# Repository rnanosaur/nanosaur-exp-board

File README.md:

# :sauropod: nanosaur expansion board - [![CC BY-NC-SA 4.0][cc-by-nc-sa-image]][cc-by-nc-sa]

NanoSaur is a little tracked robot ROS2 enabled, made for an NVIDIA Jetson Nano

* Website: [nanosaur.ai](https://nanosaur.ai)
* Do you need an help? [Discord](https://discord.gg/NSrC52P5mw)
* For technical details follow [wiki](https://github.com/rnanosaur/nanosaur/wiki)
* Something wrong? Open an [issue](https://github.com/rnanosaur/nanosaur/issues)

# How make Nanosaur PCBs on PCBWay

- Register to PCBWay using [my refferer link](https://www.pcbway.com/setinvite.aspx?inviteid=472567)
- Upon you registered, go to the <a href="https://www.pcbway.com/project/shareproject/Nanosaur___The_smallest_NVIDIA_Jetson_dinosaur_robot.html">nanosaur </a>
- Click on **"Add to Cart"** button on the right
- A pop-up will show up: all default settings are good. You must only select how many PCBs you want: the minimum quantity, by default, is 5. The first order of 5 PCBs is free on PCBWay: you must pay only the shipping costs

# Board design

This board is a simple adapter to connect the motor controller and the LCDs to the NVIDIA Jetson on your NanoSaur, this board connect:

* I2C bus 0 (Pin 27, 28)
  * oled right
* I2C bus 1 (Pin 3, 5)
  * oled left
  * adafruit motor control
* 2 custom buttons
  * GPIO Pin 31
  * GPIO Pin 33

## NVIDIA Jetson Reference

* Jetsonhacks [Jetson Nano pinout](https://www.jetsonhacks.com/nvidia-jetson-nano-j41-header-pinout/)

## Expansion board reference

Watch the documentation on [nanosaur expansion board](https://nanosaur.ai/expansion-board/)

### PCB

Layout PCB

# Develop

The documentation is made using [Kicad](https://www.kicad.org/) 5

The CI is made using
* [Kibot](https://github.com/INTI-CMNB/KiBot)
* [kicad-exports](https://github.com/nerdyscout/kicad-exports)

# License

This project is under license [Creative Commons Attribution-NonCommercial-ShareAlike 4.0 International License][cc-by-nc-sa].

[cc-by-nc-sa]: http://creativecommons.org/licenses/by-nc-sa/4.0/
[cc-by-nc-sa-image]: https://licensebuttons.net/l/by-nc-sa/4.0/88x31.png
[cc-by-nc-sa-shield]: https://img.shields.io/badge/License-CC%20BY--NC--SA%204.0-lightgrey.svg

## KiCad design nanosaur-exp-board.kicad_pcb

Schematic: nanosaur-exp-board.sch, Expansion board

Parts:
J1: jetson_nano; PinSocket_2x20_P2.54mm_Vertical
J2: Screw_Terminal_01x02; TerminalBlock_Phoenix_MPT-0,5-2-2.54_1x02_P2.54mm_Horizontal
J3, J4: Conn_i2c_oled; PinHeader_1x04_P2.54mm_Vertical
J5: Conn_motors; PinHeader_1x06_P2.54mm_Vertical
J6: Conn_buttons; PinHeader_1x03_P2.54mm_Vertical
J7: Conn_01x04; PinHeader_1x04_P2.54mm_Vertical
R1, R2: 1k; R_Axial_DIN0207_L6.3mm_D2.5mm_P10.16mm_Horizontal
SW1: SW_SPDT; slide_switch_4.7mm

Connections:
+3V3: J1.1 (3V3), J1.17 (3V3), J3.3, J4.3, J5.5, J7.3, R1.1, R2.1
GND: J1.6 (GND), J1.9 (GND), J1.14 (GND), J1.20 (GND), J1.25 (GND), J1.30 (GND), J1.34 (GND), J1.39 (GND), J2.1, J3.4, J4.4, J5.2, J5.6, J6.3, J7.4
unnamed: J1.3 (I2C_BUS1-SDA2), J4.1, J5.3, J7.1
unnamed: J1.5 (I2C_BUS1-SCL2), J4.2, J5.4, J7.2
unnamed: J1.27 (I2C_BUS0-SDA1), J3.1
unnamed: J1.28 (I2C_BUS0-SCL1), J3.2
unnamed: J1.31 (GPIO_PZ0), J6.1, R2.2
unnamed: J1.33 (GPIO_PE6), J6.2, R1.2
unnamed: J2.2, SW1.2 (B)
VCC: J1.2 (5V), J1.4 (5V), J5.1, SW1.1 (A)

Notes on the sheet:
Motors
Buttons
Display left
Display right
Optional I2C

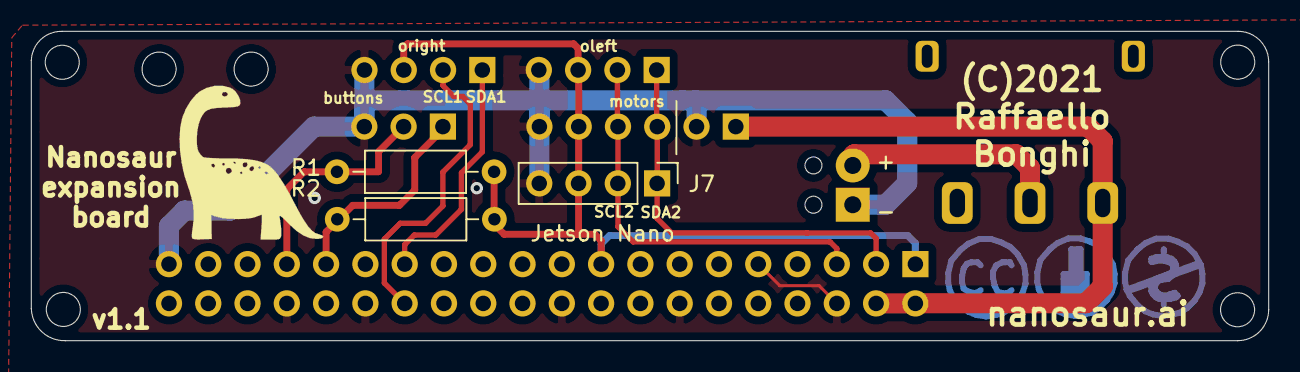
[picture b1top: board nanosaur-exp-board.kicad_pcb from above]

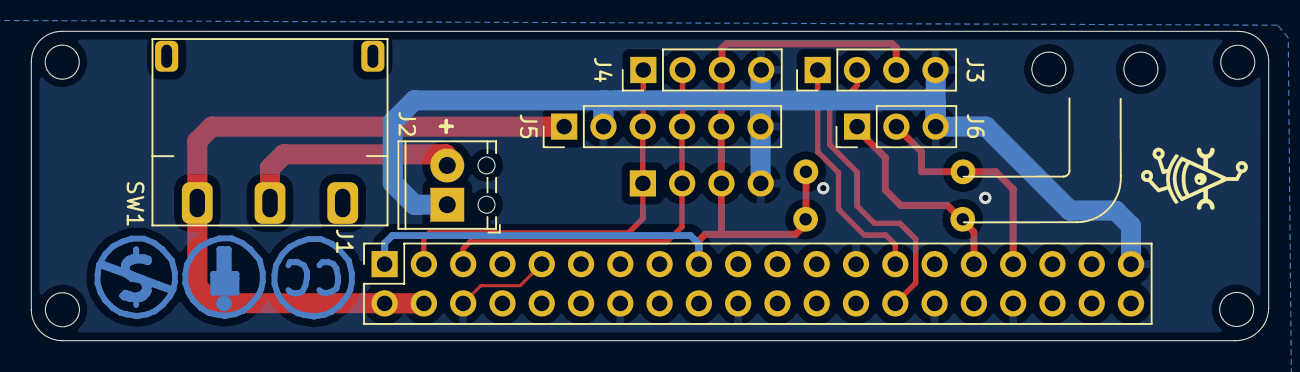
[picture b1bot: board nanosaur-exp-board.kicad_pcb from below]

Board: 2 copper layers, 80.0 x 20.0 mm, 16 parts (7 on the bottom side), 10 nets.

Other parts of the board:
H1, H2, H3, H4, H5, H6: MountingHole; MountingHole_2.2mm_M2

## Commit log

2021-02-26 Fix layout board
2021-02-26 Exp improvements
2021-02-27 Test actions
2021-02-28 Chanfe from kibot action to kicad-exports
2021-02-28 New workflow test
2021-03-01 Improve kibot output
2021-03-01 fix pcbdraw
2021-03-01 improve tag push
2021-03-01 test output
2021-03-01 fix workflow
2021-03-01 test output asset
2021-03-01 Improve data generation
2021-03-01 Fix pdf combine
2021-03-01 Test combine
2021-03-01 Add scripts
2021-03-01 Fix combine
2021-03-01 fix script pdf
2021-03-01 Fix path
2021-03-01 Final fix
2021-03-01 combine-pdf
2021-03-01 Improve tag release
2021-03-01 release fix
2021-03-01 fix image push
2021-03-01 Check conating folder assets
2021-03-01 Fix path assets
2021-03-01 Fix assets
2021-03-02 Add convert pdf
2021-03-02 Test push images to nanosaur webpage
2021-03-02 Fix username
2021-03-02 Update workflow
2021-03-02 Fix id
2021-03-02 Improve workflow and README
2021-03-02 Fix gitignore
2021-03-04 Rework of schematic
    I reworked the schematic and added adapters so the Users has less to solder. Please note that these changes are currently only in the schematic not the PCB side of things. These changes will ba added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
    Signed off by: Thore Krug
2021-03-29 Added first rev of exp board
    Added first revision of the expansion Board.
    Note ! Board is work in progress.
2021-05-05 improve expansion board and fix schematic
2021-05-05 minor fixes
2021-05-08 Enable drc on kibot
2021-05-08 Improve kibot exporter
2021-05-08 Improve kibot
2021-05-08 improve workflow
2021-05-08 Add gerber
2021-05-08 test footprint libraries
2021-05-08 Improve sch and pcb
2021-05-08 Improve pcb
2021-05-09 fix kibot svg
2021-05-09 Fix readme
2021-05-09 Improve sch and azz gerber zip
2021-05-09 Fix CI
2021-05-09 Test gerber zip
2021-05-09 Improve gerber
2021-05-09 Fix kibot and pcb
2021-05-10 Improve PCB layout, fix BOM, improve sch
2021-05-10 Final PCB fix
2021-05-10 fix bom
2021-06-08 Fix license and minor fixes
2021-07-05 Fix DRC
2021-07-07 Fix dependabot
2021-07-07 Bump dmnemec/copy_file_to_another_repo_action from 1.0.4 to 1.1.1
    Bumps [dmnemec/copy_file_to_another_repo_action](https://github.com/dmnemec/copy_file_to_another_repo_action) from 1.0.4 to 1.1.1.
    - [Release notes](https://github.com/dmnemec/copy_file_to_another_repo_action/releases)
    - [Commits](https://github.com/dmnemec/copy_file_to_another_repo_action/compare/v1.0.4...v1.1.1)
    ---
    updated-dependencies:
    - dependency-name: dmnemec/copy_file_to_another_repo_action
2021-07-07 Bump nerdyscout/kicad-exports from 2.2 to 2.3
    Bumps [nerdyscout/kicad-exports](https://github.com/nerdyscout/kicad-exports) from 2.2 to 2.3.
    - [Release notes](https://github.com/nerdyscout/kicad-exports/releases)
    - [Changelog](https://github.com/nerdyscout/kicad-exports/blob/main/CHANGELOG.md)
    - [Commits](https://github.com/nerdyscout/kicad-exports/compare/v2.2...v2.3)
    ---
    updated-dependencies:
2021-12-27 Reference buy url
2021-12-29 Added other documentation fields
2021-12-29 fix table fields
2021-12-29 Rearrange CI
2021-12-29 Fix gerber zip build
2022-03-02 Bump actions/checkout from 2 to 3
    Bumps [actions/checkout](https://github.com/actions/checkout) from 2 to 3.
    - [Release notes](https://github.com/actions/checkout/releases)
    - [Changelog](https://github.com/actions/checkout/blob/main/CHANGELOG.md)
    - [Commits](https://github.com/actions/checkout/compare/v2...v3)
    ---
    updated-dependencies:
2022-04-08 Bump actions/download-artifact from 2 to 3
    Bumps [actions/download-artifact](https://github.com/actions/download-artifact) from 2 to 3.
    - [Release notes](https://github.com/actions/download-artifact/releases)
    - [Commits](https://github.com/actions/download-artifact/compare/v2...v3)
    ---
    updated-dependencies:
    - dependency-name: actions/download-artifact
2022-04-08 Bump actions/upload-artifact from 2 to 3
    Bumps [actions/upload-artifact](https://github.com/actions/upload-artifact) from 2 to 3.
    - [Release notes](https://github.com/actions/upload-artifact/releases)
    - [Commits](https://github.com/actions/upload-artifact/compare/v2...v3)
    ---
    updated-dependencies:
    - dependency-name: actions/upload-artifact
2023-09-04 Bump actions/checkout from 3 to 4
    Bumps [actions/checkout](https://github.com/actions/checkout) from 3 to 4.
    - [Release notes](https://github.com/actions/checkout/releases)
    - [Changelog](https://github.com/actions/checkout/blob/main/CHANGELOG.md)
    - [Commits](https://github.com/actions/checkout/compare/v3...v4)
    ---
    updated-dependencies:
